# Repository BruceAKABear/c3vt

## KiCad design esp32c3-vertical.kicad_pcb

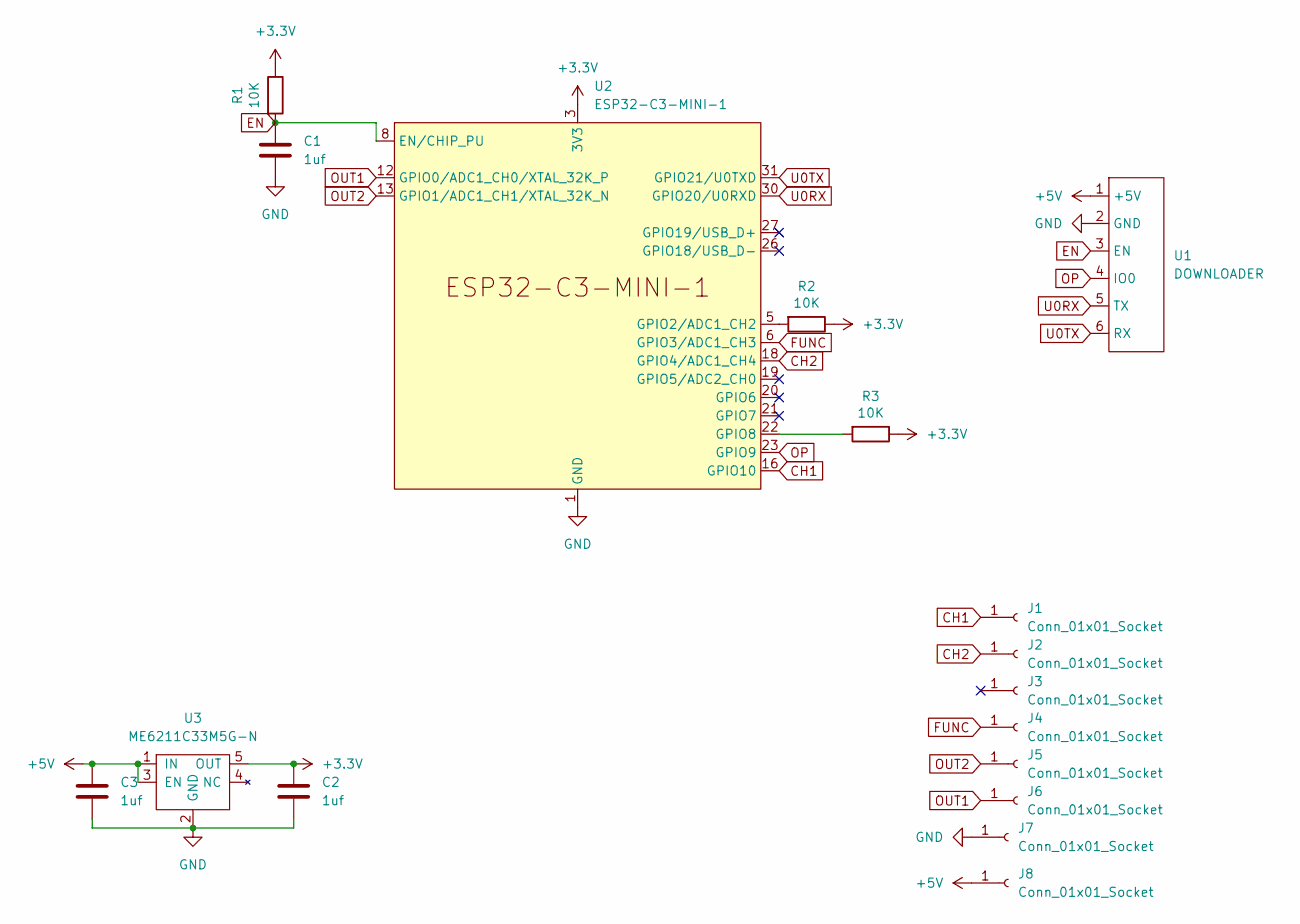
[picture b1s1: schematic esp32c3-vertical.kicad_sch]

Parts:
C1, C2, C3: 1uf; C_0603_1608Metric
J1, J2, J3, J4, J5, J6, J7, J8: Conn_01x01_Socket; CON_1X2
R1, R2, R3: 10K; R_0603_1608Metric
U1: DOWNLOADER
U2: ESP32-C3-MINI-1
U3: ME6211C33M5G-N; SOT-23-5

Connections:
+3.3V: C2.1, R1.1, R2.1, R3.1, U2.3 (3V3), U3.5 (OUT)
+5V: C3.1, J8.1, U1.1 (+5V), U3.1 (IN), U3.3 (EN)
CH1: J1.1, U2.16 (GPIO10)
CH2: J2.1, U2.18 (GPIO4/ADC1_CH4)
EN: C1.1, R1.2, U1.3 (EN), U2.8 (EN/CHIP_PU)
FUNC: J4.1, U2.6 (GPIO3/ADC1_CH3)
GND: C1.2, C2.2, C3.2, J7.1, U1.2 (GND), U2.1 (GND), U2.2 (GND), U2.11 (GND), U2.14 (GND), U2.36 (GND), U2.37 (GND), U2.38 (GND), U2.39 (GND), U2.40 (GND), U2.41 (GND), U2.42 (GND), U2.43 (GND), U2.44 (GND), U2.45 (GND), U2.46 (GND), U2.47 (GND), U2.48 (GND), U2.49 (GND), U2.50 (GND), U2.51 (GND), U2.52 (GND), U2.53 (GND), U3.2 (GND)
unnamed: R2.2, U2.5 (GPIO2/ADC1_CH2)
unnamed: R3.2, U2.22 (GPIO8)
OP: U1.4 (IO0), U2.23 (GPIO9)
OUT1: J6.1, U2.12 (GPIO0/ADC1_CH0/XTAL_32K_P)
OUT2: J5.1, U2.13 (GPIO1/ADC1_CH1/XTAL_32K_N)
U0RX: U1.5 (TX), U2.30 (GPIO20/U0RXD)
U0TX: U1.6 (RX), U2.31 (GPIO21/U0TXD)

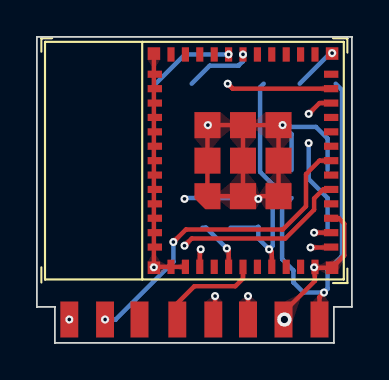
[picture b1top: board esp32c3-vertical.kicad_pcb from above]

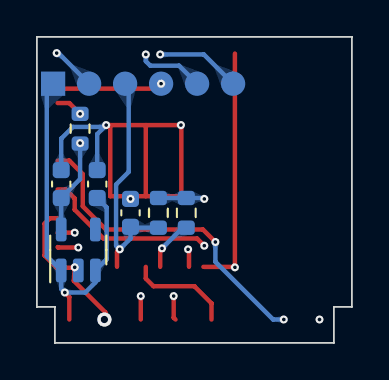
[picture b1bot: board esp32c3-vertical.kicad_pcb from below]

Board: 4 copper layers, 17.5 x 17.0 mm, 17 parts (8 on the bottom side), 14 nets.

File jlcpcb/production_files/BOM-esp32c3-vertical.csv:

Comment,Designator,Footprint,LCSC
DOWNLOADER,U1,DOWNLOADER,
1uf,C3,C_0603_1608Metric,
1uf,C2,C_0603_1608Metric,
Conn_01x01_Socket,J8,CON_1X2,
Conn_01x01_Socket,J7,CON_1X2,
Conn_01x01_Socket,J6,CON_1X2,
Conn_01x01_Socket,J5,CON_1X2,
Conn_01x01_Socket,J4,CON_1X2,
Conn_01x01_Socket,J3,CON_1X2,
Conn_01x01_Socket,J2,CON_1X2,
Conn_01x01_Socket,J1,CON_1X2,
ME6211C33M5G-N,U3,SOT-23-5,
1uf,C1,C_0603_1608Metric,
10K,R1,R_0603_1608Metric,
10K,R3,R_0603_1608Metric,
ESP32-C3-MINI-1,U2,ESP32-C3-MINI-1,
10K,R2,R_0603_1608Metric,

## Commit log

2024-05-22 init
